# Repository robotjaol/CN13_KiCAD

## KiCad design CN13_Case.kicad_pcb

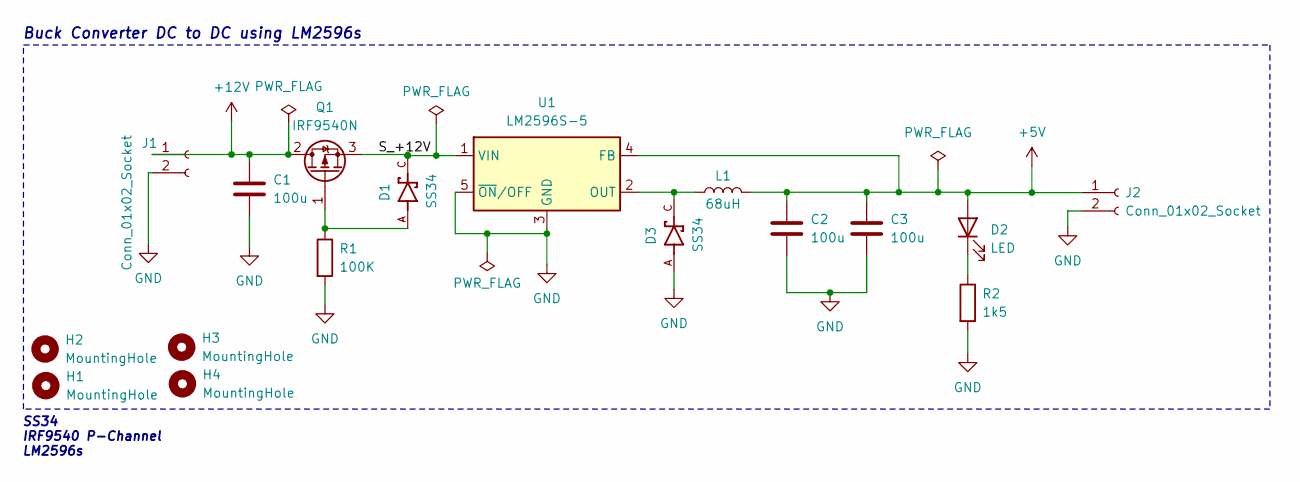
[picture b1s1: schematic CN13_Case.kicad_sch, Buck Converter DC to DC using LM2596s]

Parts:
C1, C2, C3: 100u; CAP_63V100UF
D1, D3: SS34; DIO_SS34; PARTREV S2311
D2: LED; LED_1206_3216Metric_Pad1.42x1.75mm_HandSolder
H1, H2, H3, H4: MountingHole; MountingHole_3.2mm_M3
J1, J2: Conn_01x02_Socket; PhoenixContact_GMSTBVA_2,5_2-G-7,62_1x02_P7.62mm_Vertical
L1: 68uH; SRR1260-330M
Q1: IRF9540N; TO-220-3_Vertical
R1: 100K; R_1206_3216Metric_Pad1.30x1.75mm_HandSolder
R2: 1k5; R_1206_3216Metric_Pad1.30x1.75mm_HandSolder
U1: LM2596S-5; TO-263-5_TabPin3

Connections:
+5V: C2.1, C3.1, D2.2 (A), J2.1, L1.2, U1.4 (FB)
+12V: C1.1, J1.1, Q1.2 (D)
/S_+12V: D1.C, Q1.3 (S), U1.1 (VIN)
GND: C1.2, C2.2, C3.2, D3.A, J1.2, J2.2, R1.2, R2.2, U1.3 (GND), U1.5 (~ON/OFF)
unnamed: D2.1 (K), R2.1
unnamed: D1.A, Q1.1 (G), R1.1
unnamed: D3.C, L1.1, U1.2 (OUT)

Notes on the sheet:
SS34 IRF9540 P-Channel LM2596s
Buck Converter DC to DC using LM2596s

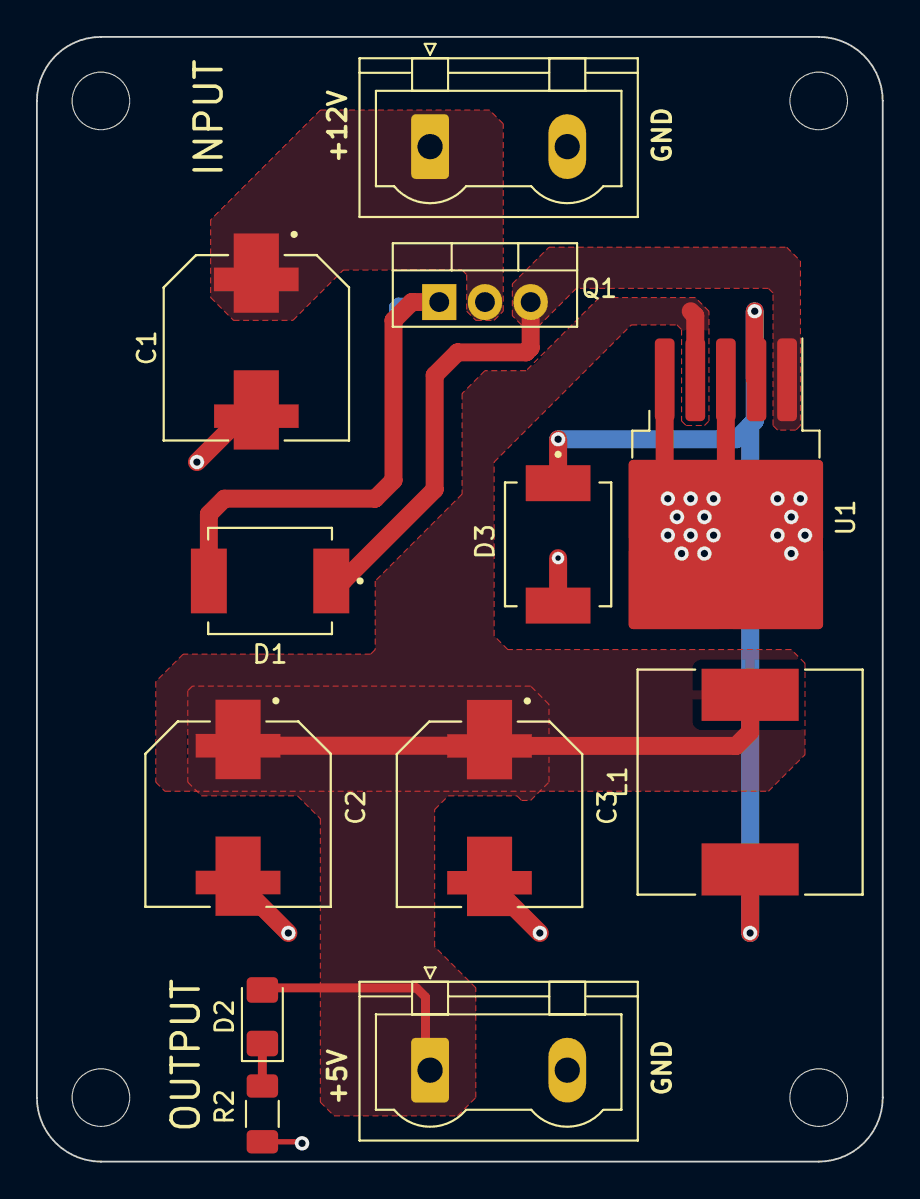
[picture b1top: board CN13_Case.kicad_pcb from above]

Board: 2 copper layers, 47.0 x 62.5 mm, 17 parts (1 on the bottom side), 7 nets.

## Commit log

2024-02-24 CN13 KiCAD
2024-02-24 add : Image Buck Converter
